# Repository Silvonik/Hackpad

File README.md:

# Hackpad
## About
The Hackpad is a custom macropad to help me with everyday repetitive keyboard shorcuts.

Instead of pressing ctrl and c to copy or ctrl and s to save I now only need to press one key on the Hackpad.

The point of the Hackpad was to teach me how to make hardware and also to let me avoid getting my hands to awkward positions just to undo or save my code.

## How I made the Hackpad
To make the Hackpad I needed to learn how to make a Schematic, PCB, and Case, but the problem was I never done it before so first thing I did is come up with the idea of what the Hackpad will do,
after I came up with the idea of the shortcuts. Then I the got to work by making the schematic, to make it I followed the guide and asked questions to the Hackpad Channel on Slack. 
When the schematic was finished I turned it into a PCB, I enjoyed working on the PCB it is very relaxing but not really when you run into problems.
After The PCB I worked on the Case, I installed Fusion360 for the first time and started making the case, The case took me the longest because I kept having to reset or go back and change stuff and it was very confusing to me as a beginner.
After all of that I went to sleep and in the morning worked on the Firmware. the firmware was okay because I used Arduino IDE which I previously used before, when finished the code I quickly compiled it to check if it worked which it did not but after some deubuging everything worked.
After an eternity I finally got all the parts needed to assemble the Hackpad, first I soldered the header pins to the Xiao RP2040, after I uploaded the firmware and tested the circuit with a breadboard and it worked, then I put all the parts on the PCB and I soldered them on, when I finished that I tried to put in inside the case with the cover but it didn't fit so I had to remodel the case and 3D print a new one, so after all of that I now have a macropad which I use daily and It came out AMAZING!

## Features
Ctrl A = All,
Ctrl C = copy,
Ctrl V = paste,
Ctrl S = save,
Ctrl Z = undo,
Ctrl Y = Redo.

## Challenges
It was very hard learning everything from scratch like how to make a schematic, pcb, a case but I managed and I couldn't have done it without [yam]([https://example.com](https://github.com/haohaohaoyan))
he helped me so much with like bugs and common problems my beginner brain didn't now how to solve.

## What I Learned
When building the Hackpad I learned how to make a PCB, use Kicad, make a schematic, use Fusion360 to make the case and how to actually solder.
These skills will help me in my future hardware projects so much!

## Photos

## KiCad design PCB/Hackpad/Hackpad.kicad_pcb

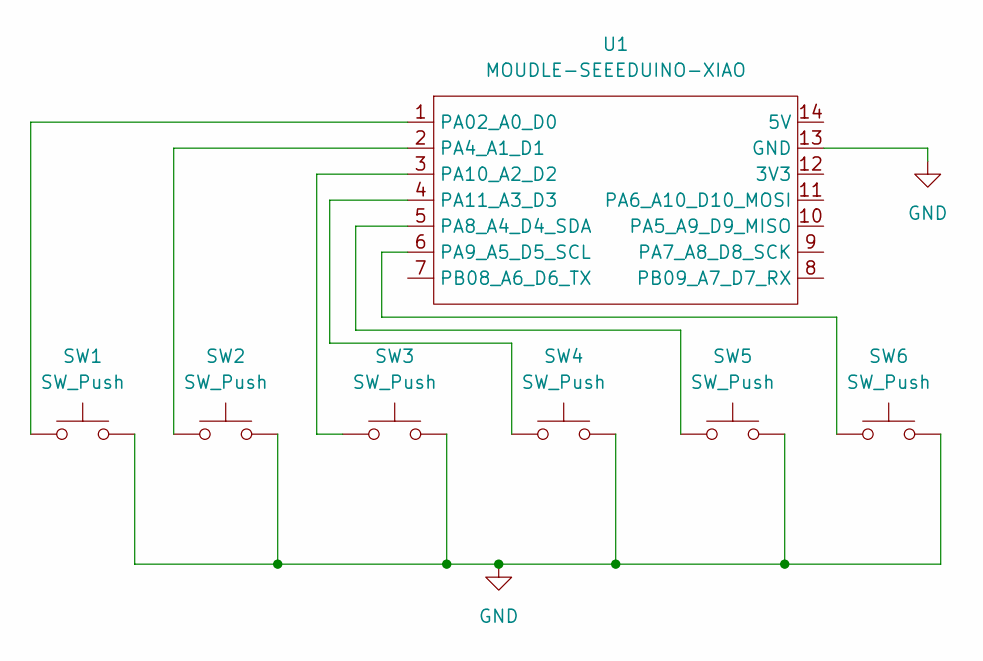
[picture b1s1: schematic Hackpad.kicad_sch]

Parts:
SW1, SW2, SW3, SW4, SW5, SW6: SW_Push; SW_Cherry_MX_1.00u_PCB
U1: MOUDLE-SEEEDUINO-XIAO; XIAO-Generic-Hybrid-14P-2.54-21X17.8MM

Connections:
GND: SW1.2, SW2.2, SW3.2, SW4.2, SW5.2, SW6.2, U1.13 (GND)
unnamed: SW1.1, U1.1 (PA02_A0_D0)
unnamed: SW2.1, U1.2 (PA4_A1_D1)
unnamed: SW5.1, U1.5 (PA8_A4_D4_SDA)
unnamed: SW6.1, U1.6 (PA9_A5_D5_SCL)
unnamed: SW3.1, U1.3 (PA10_A2_D2)
unnamed: SW4.1, U1.4 (PA11_A3_D3)

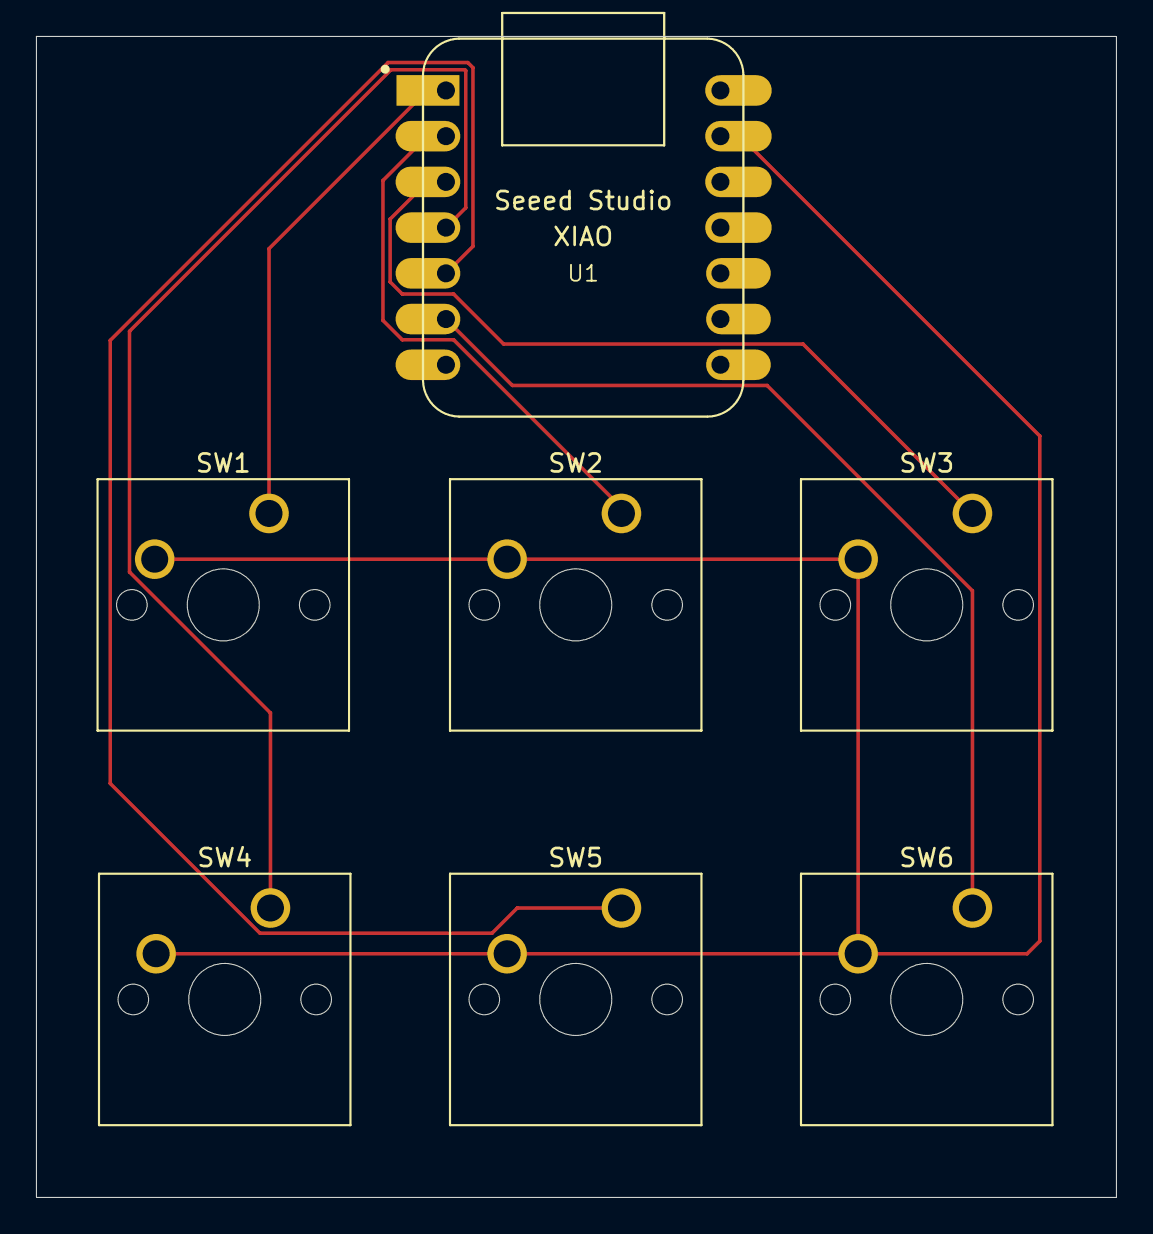
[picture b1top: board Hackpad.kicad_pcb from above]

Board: 2 copper layers, 60.0 x 64.5 mm, 7 parts (0 on the bottom side), 7 nets.
